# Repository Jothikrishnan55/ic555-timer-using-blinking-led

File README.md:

555 Timer LED Blinker

A simple LED blinker circuit built around the NE555P timer IC, designed as a complete PCB project in KiCad — from schematic capture through to manufacturing-ready Gerber files.

Overview

This is a classic astable (self-triggering) 555 timer circuit that blinks an LED on and off at a fixed rate. It was built as a first hands-on project to learn the full PCB design workflow: schematic design, component selection, electrical rule checking, PCB layout, and generating files for fabrication.

Components Used

Component	Value / Part	Function

U1	NE555P	Timer IC, configured in astable mode to generate the blink signal

R1	10kΩ Resistor	Timing resistor

R2	1kΩ Resistor	Timing resistor

C1	0.01µF Ceramic Capacitor	Stabilizing capacitor (pin 5, CV)

C2	10µF Electrolytic Capacitor	Timing capacitor (sets the blink rate)

R3	220Ω Resistor	LED current-limiting resistor

D1	LED	Visual blink output

TP1	Test Point (battery)	Power input connection point

How It Works

Power: The circuit is powered through a test point (TP1), standing in for a 9V battery connection — VCC and GND rails feed the 555 timer.

Timing network: R1 and R2 are connected to the DISCHARGE (pin 7) and THRESHOLD (pin 6) pins, with C2 (10µF) forming the RC timing loop that sets how fast the circuit charges and discharges. This combination directly controls the blink rate.

Stabilizing capacitor: C1 (0.01µF) sits on the CONTROL VOLTAGE pin (pin 5) to ground, keeping the timer's internal reference voltage stable and preventing erratic triggering.

Output: Pin 3 (OUTPUT) switches HIGH and LOW at the timing rate set by R1, R2, and C2. This output drives R3, which limits current to the LED (D1), making it blink on and off.

Reset: Pin 4 (RESET) is tied to VCC to keep the timer continuously enabled.

Design Process

Schematic captured in KiCad, with all components wired according to the standard 555 astable configuration.

Verified using KiCad's Electrical Rules Checker (ERC).

PCB layout completed with component placement and routing.

Gerber files generated for manufacturing.

Files Included

.kicad_sch — Schematic source file
.kicad_pcb — PCB layout file
.kicad_pro — KiCad project file
Gerber files — Ready for PCB manufacturing

Tools Used

KiCad — schematic capture, PCB layout, and Gerber generation
Status

Design complete. First hands-on PCB design project, built to learn the end-to-end KiCad workflow.

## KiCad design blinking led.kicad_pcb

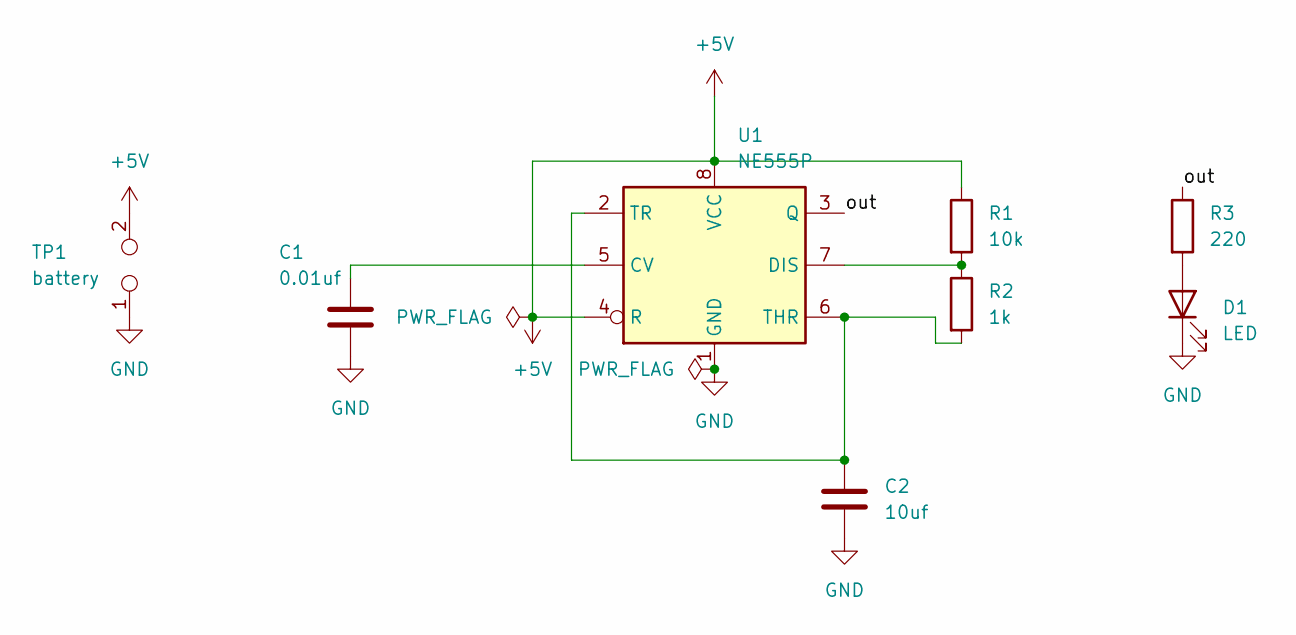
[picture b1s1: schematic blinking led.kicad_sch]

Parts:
C1: 0.01uf; C_Disc_D3.0mm_W2.0mm_P2.50mm
C2: 10uf; C_Radial_D5.0mm_H5.0mm_P2.00mm
D1: LED; LED_D5.0mm
R1: 10k; R_Axial_DIN0207_L6.3mm_D2.5mm_P2.54mm_Vertical
R2: 1k; R_Axial_DIN0207_L6.3mm_D2.5mm_P2.54mm_Vertical
R3: 220; R_Axial_DIN0207_L6.3mm_D2.5mm_P2.54mm_Vertical
TP1: battery; PinSocket_2x01_P2.00mm_Vertical
U1: NE555P; DIP-8_W7.62mm

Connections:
+5V: R1.1, TP1.2, U1.4 (R), U1.8 (VCC)
/out: R3.1, U1.3 (Q)
GND: C1.2, C2.2, D1.1 (K), TP1.1, U1.1 (GND)
unnamed: D1.2 (A), R3.2
unnamed: C1.1, U1.5 (CV)
unnamed: R1.2, R2.1, U1.7 (DIS)
unnamed: C2.1, R2.2, U1.2 (TR), U1.6 (THR)

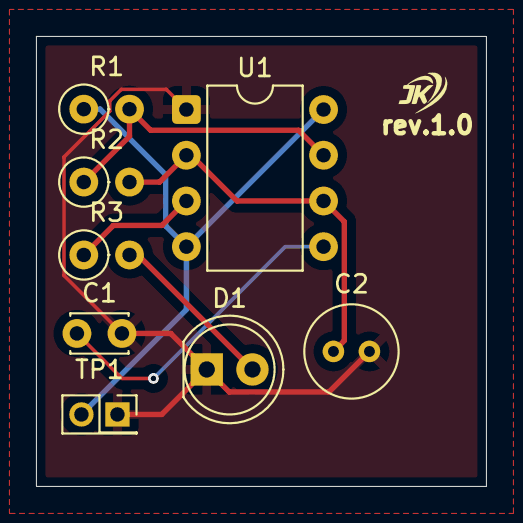
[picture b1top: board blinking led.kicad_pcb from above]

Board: 2 copper layers, 25.0 x 25.0 mm, 8 parts (0 on the bottom side), 7 nets.
